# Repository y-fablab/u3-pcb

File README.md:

# Useless Machine V3

KiCad projet for a useless machine based on ESP8266.

# License

Copyright (c) 2020 Y-FABLAB

Licensed under the [Creative Commons CC-BY 4.0 License](https://creativecommons.org/licenses/by/4.0/legalcode).

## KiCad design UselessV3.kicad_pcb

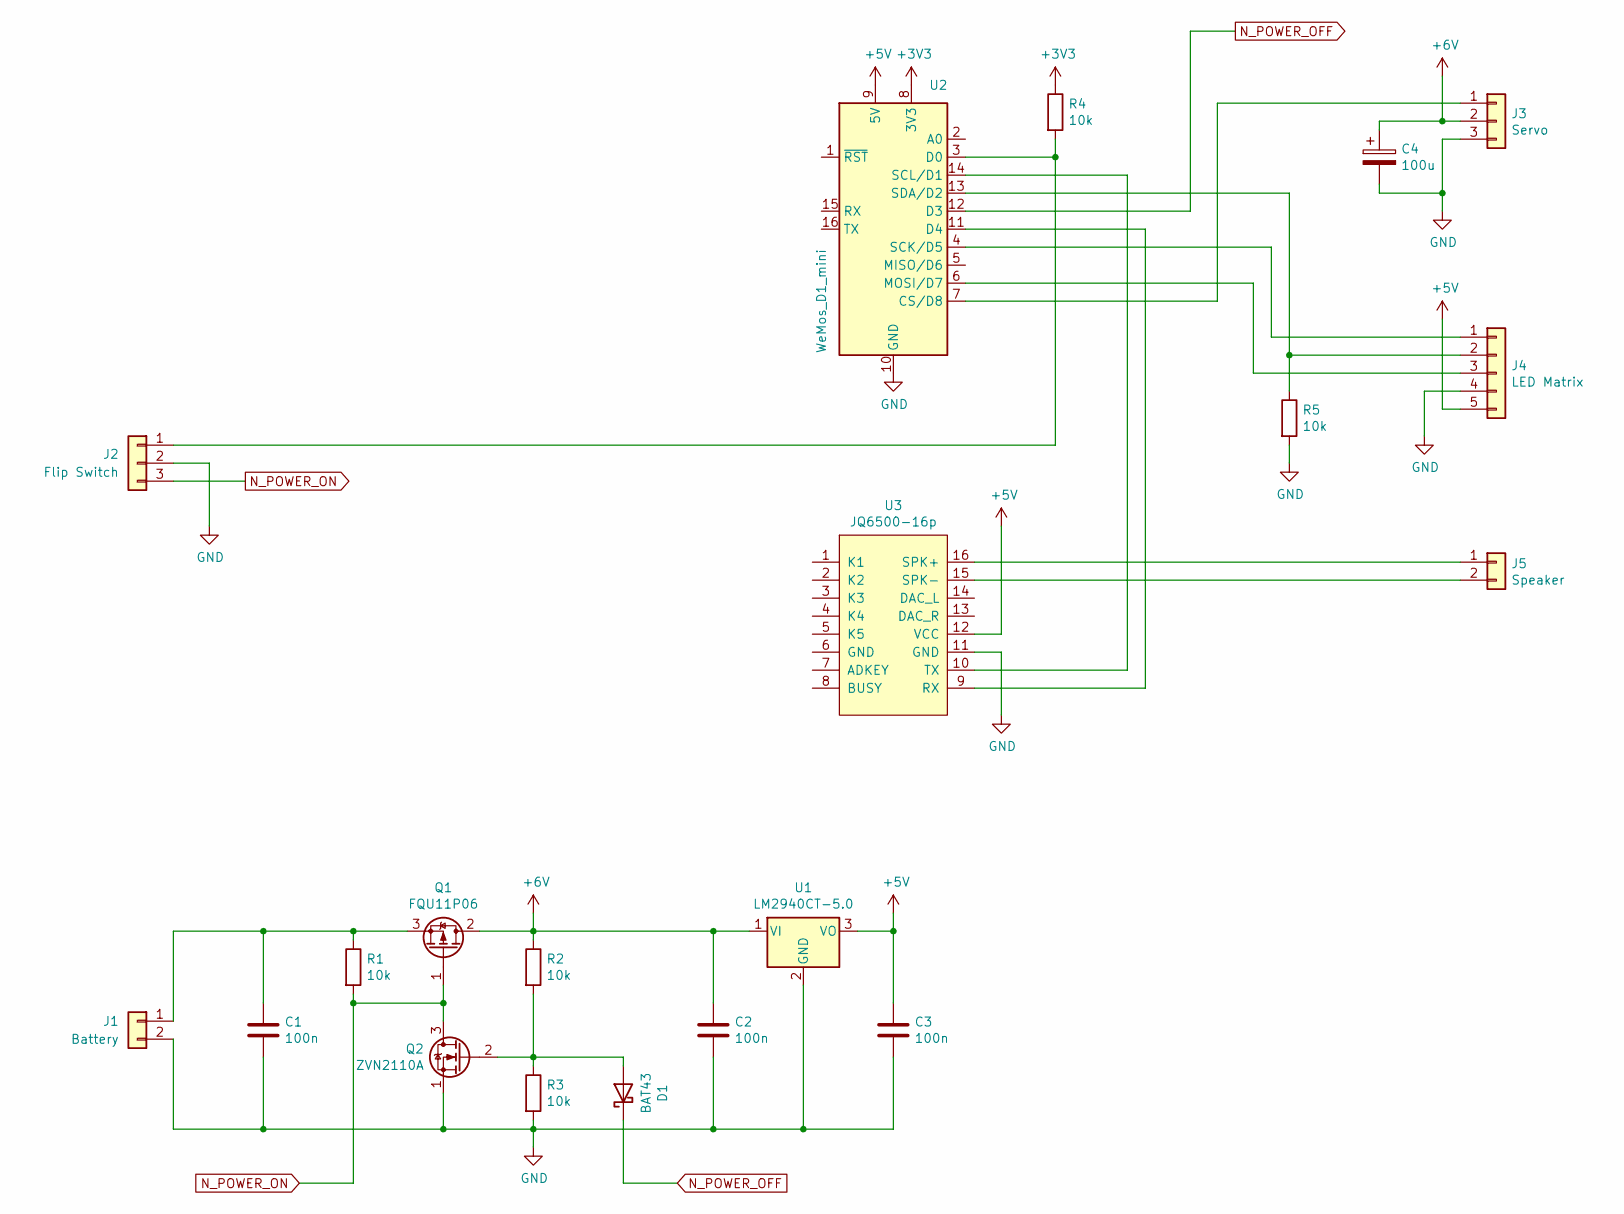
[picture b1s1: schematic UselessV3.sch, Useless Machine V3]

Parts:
C1, C2, C3: 100n; C_Rect_L4.6mm_W2.0mm_P2.50mm_MKS02_FKP02
C4: 100u; CP_Radial_D6.3mm_P2.50mm
D1: BAT43; D_DO-35_SOD27_P7.62mm_Horizontal
J1: Battery; PinHeader_1x02_P2.54mm_Vertical
J2: Flip Switch; PinHeader_1x03_P2.54mm_Vertical
J3: Servo; PinHeader_1x03_P2.54mm_Vertical
J4: LED Matrix; PinHeader_1x05_P2.54mm_Vertical
J5: Speaker; PinHeader_1x02_P2.54mm_Vertical
Q1: FQU11P06; TO-251-3_Vertical
Q2: ZVN2110A; TO-92L_HandSolder
R1, R2, R3, R4, R5: 10k; R_Axial_DIN0207_L6.3mm_D2.5mm_P7.62mm_Horizontal
U1: LM2940CT-5.0; TO-220-3_Vertical
U2: WeMos_D1_mini; WEMOS_D1_mini_light
U3: JQ6500-16p

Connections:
+3V3: R4.1, U2.8 (3V3)
+5V: C3.1, J4.5, U1.3 (VO), U2.9 (5V), U3.12 (VCC)
+6V: C2.1, C4.1, J3.2, Q1.2 (D), R2.1, U1.1 (VI)
GND: C1.2, C2.2, C3.2, C4.2, J1.2, J2.2, J3.3, J4.4, Q2.1 (S), R3.2, R5.2, U1.2 (GND), U2.10 (GND), U3.11 (GND)
N_POWER_OFF: D1.1 (K), U2.12 (D3)
N_POWER_ON: J2.3, Q1.1 (G), Q2.3 (D), R1.2
unnamed: C1.1, J1.1, Q1.3 (S), R1.1
unnamed: D1.2 (A), Q2.2 (G), R2.2, R3.1
unnamed: J2.1, R4.2, U2.3 (D0)
unnamed: J3.1, U2.7 (CS/D8)
unnamed: J4.1, U2.4 (SCK/D5)
unnamed: J4.2, R5.1, U2.13 (SDA/D2)
unnamed: J4.3, U2.6 (MOSI/D7)
unnamed: J5.1, U3.16 (SPK+)
unnamed: J5.2, U3.15 (SPK-)
unnamed: U2.11 (D4), U3.9 (RX)
unnamed: U2.14 (SCL/D1), U3.10 (TX)

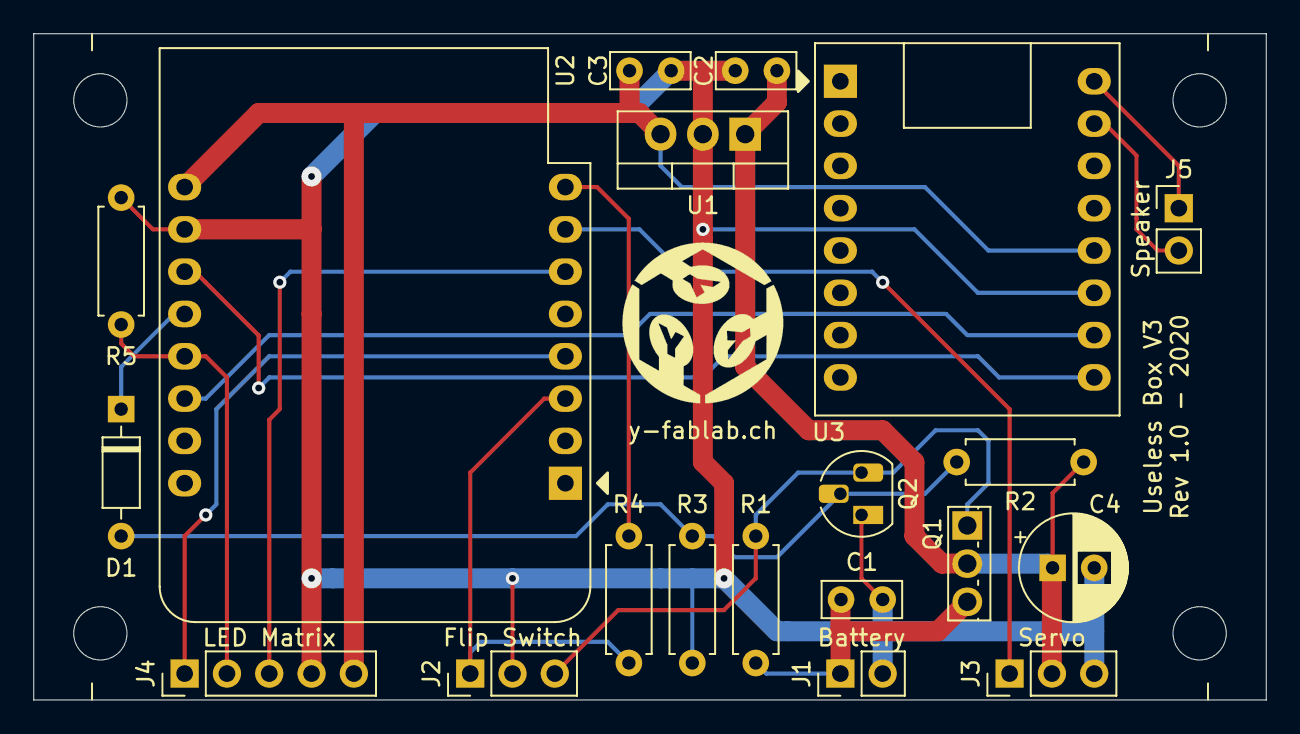
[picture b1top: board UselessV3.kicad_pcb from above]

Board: 2 copper layers, 74.0 x 40.0 mm, 20 parts (0 on the bottom side), 17 nets.

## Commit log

2020-07-19 initial design
2020-07-19 add schematics
2020-07-19 add 3d image
2020-07-19 add readme file

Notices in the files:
UselessV3.sch:
Licensed under CC BY 4.0
Copyright (c) 2020 y-fablab.ch
